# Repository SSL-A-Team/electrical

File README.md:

# Getting Started with A-Team Electrical

All current board releases use KiCad 7.X. 

See [releases](https://github.com/SSL-A-Team/electrical/releases) for competition production files. Our releases include known bug documentation, and the confirmed gerber, BoM, and CPL files sent to fab so you know you're looking and ordering what we did. Releases are accompanied by a tagged commit, for all editable project files used to generate the fab products.

For complex boards like control and kicker, we include spice models and python files that compute any relevant values from datasheets, and including documented references and links to needed formulations. 

## Setting Up KiCAD

### Setting Up the KiCAD Library Path
- Click `Preferences->Configure Paths`
- Under `Environment Variables` click `+`
- Set the name `LIB_DIR_AT`
- Set the path to `<repository_location>/lib` where \<repository_location\> is the download location.

Example entry:
- Name: `LIB_DIR_AT`
- Path: `C:\Users\guyfl\Documents\A-Team\electrical\lib`

### Setting Up JLCPCB Plugin

KiCAD version 6.99 (nightly) or newer should install the [KiCAD JLCPCB Tools](https://github.com/Bouni/kicad-jlcpcb-tools) plugin. 

## Setting Up the Python Environment
 1. We recommend creating a python environment using `python3 -m venv venv` (python 10 appears to be required)
 2. Install poetry `pip install poetry`
 3. Run any python file with `poetry run python <python_file>`
 4. (Optional) Add dependencies with `poetry add <dependency>`

## Soldering

Our [soldering process](SOLDERING.md) is documented. Advanced components like modern SMPS chips and current sense motor hardware proved sensitive to technique. The team's tries to PCBA as much as possible, but sometime it's too expensive to PCBA all chips, especially advanced ones not in stock at the fab house.

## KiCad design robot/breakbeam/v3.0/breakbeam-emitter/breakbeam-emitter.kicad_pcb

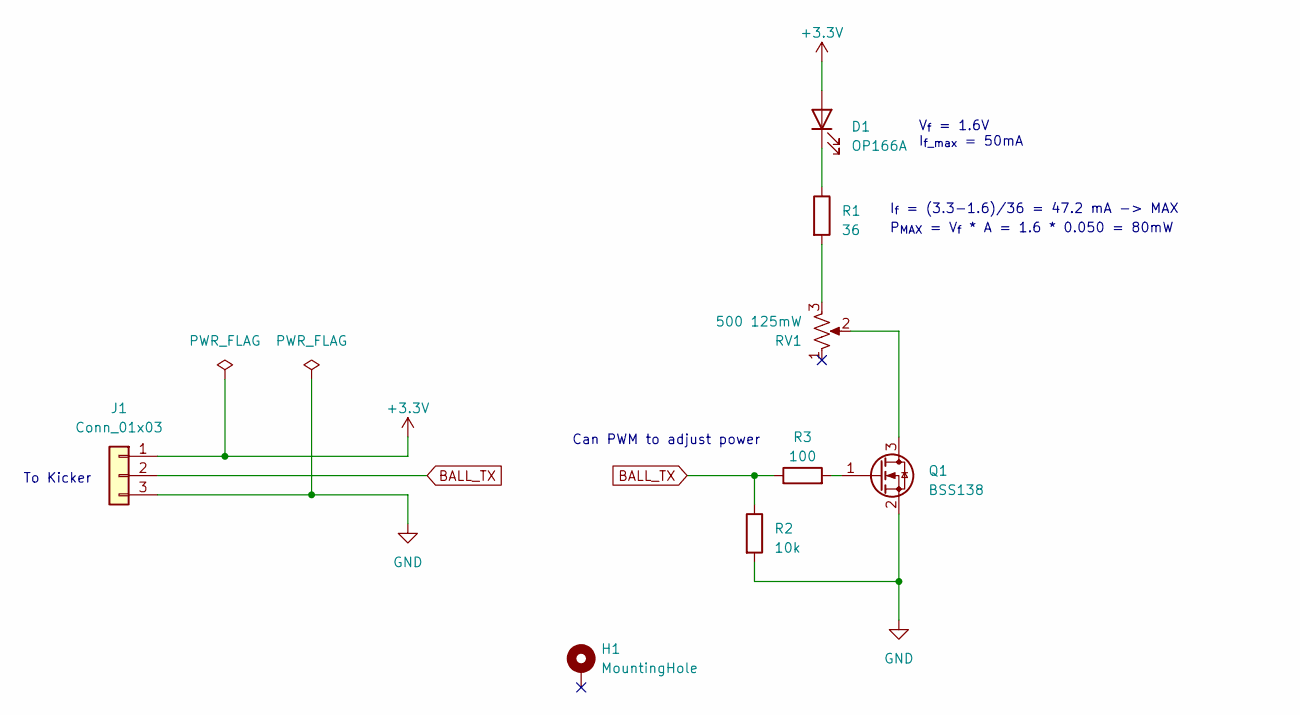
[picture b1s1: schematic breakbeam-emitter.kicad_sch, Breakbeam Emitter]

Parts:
D1: OP166A; LED_D3.0mm
H1: MountingHole; MountingHole_3.2mm_M3_ISO7380_Pad
J1: Conn_01x03; JST_SH_SM03B-SRSS-TB_1x03-1MP_P1.00mm_Horizontal; LCSC C160403
Q1: BSS138; SOT-23; LCSC C82045
R1: 36; R_0603_1608Metric_Pad0.98x0.95mm_HandSolder; LCSC C101000
R2: 10k; R_0603_1608Metric_Pad0.98x0.95mm_HandSolder; LCSC C25804
R3: 100; R_0603_1608Metric_Pad0.98x0.95mm_HandSolder; LCSC C22775
RV1: 500 125mW; Potentiometer_Bourns_TC33X_Vertical; LCSC C720649

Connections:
+3.3V: D1.2 (A), J1.1
BALL_TX: J1.2, R2.1, R3.1
GND: J1.3, Q1.2 (S), R2.2
unnamed: D1.1 (K), R1.1
unnamed: Q1.3 (D), RV1.2
unnamed: Q1.1 (G), R3.2
unnamed: R1.2, RV1.3

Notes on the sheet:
P_{MAX} = V_{f} * A = 1.6 * 0.050 = 80mW
I_{f} = (3.3-1.6)/36 = 47.2 mA -> MAX
To Kicker
V_{f} = 1.6V I_{f_max} = 50mA
Can PWM to adjust power

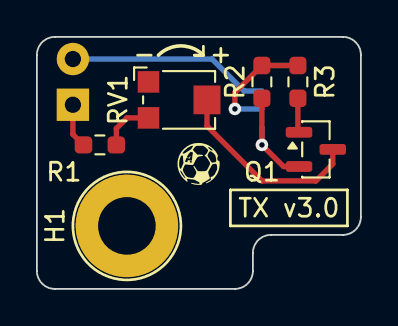
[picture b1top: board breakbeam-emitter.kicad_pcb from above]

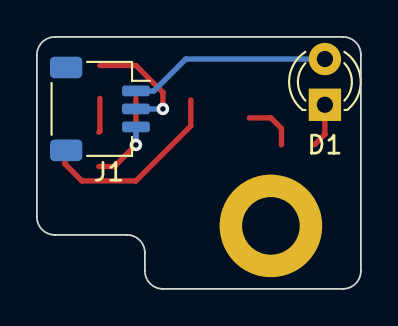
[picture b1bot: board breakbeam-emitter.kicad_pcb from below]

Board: 2 copper layers, 18.0 x 14.0 mm, 8 parts (2 on the bottom side), 7 nets.

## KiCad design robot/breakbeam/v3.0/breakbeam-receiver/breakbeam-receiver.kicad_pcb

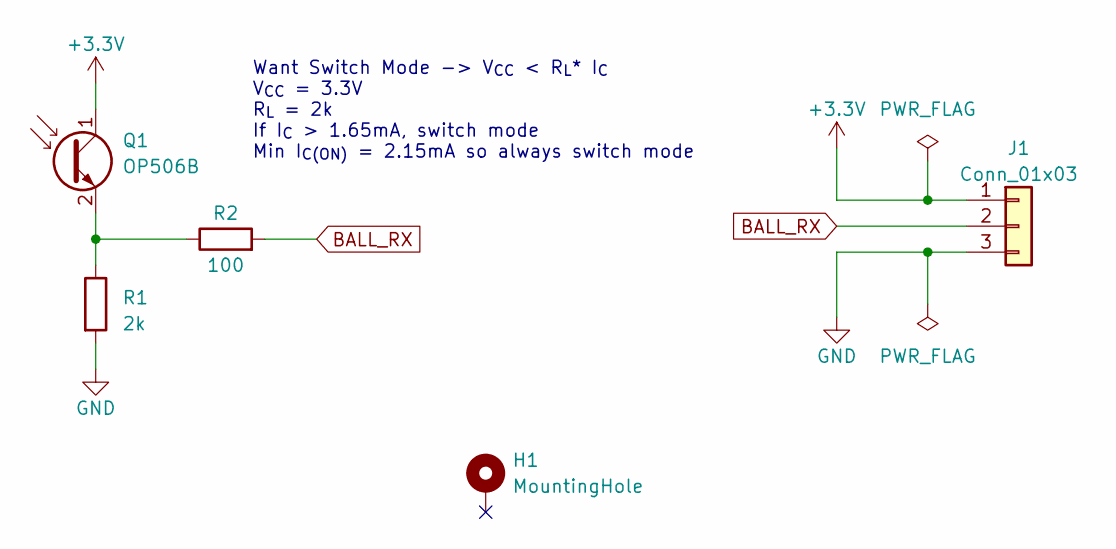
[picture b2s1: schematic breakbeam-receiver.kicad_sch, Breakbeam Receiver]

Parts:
H1: MountingHole; MountingHole_3.2mm_M3_ISO7380_Pad
J1: Conn_01x03; JST_SH_SM03B-SRSS-TB_1x03-1MP_P1.00mm_Horizontal; LCSC C160403
Q1: OP506B; LED_D3.0mm
R1: 2k; R_0603_1608Metric; LCSC C22975
R2: 100; R_0603_1608Metric; LCSC C22775

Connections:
+3.3V: J1.1, Q1.1 (C)
BALL_RX: J1.2, R2.2
GND: J1.3, R1.2
unnamed: Q1.2 (E), R1.1, R2.1

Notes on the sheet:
Want Switch Mode -> V_{CC} < R_{L}* I_{C} V_{CC} = 3.3V R_{L} = 2k If I_{C} > 1.65mA, switch mode Min I_{C(ON)} = 2.15mA so always switch mode

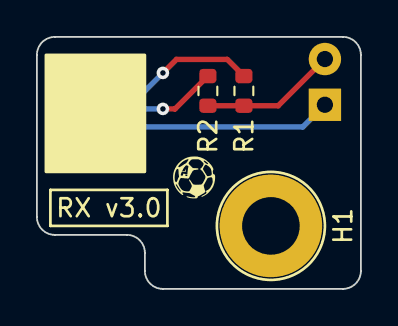
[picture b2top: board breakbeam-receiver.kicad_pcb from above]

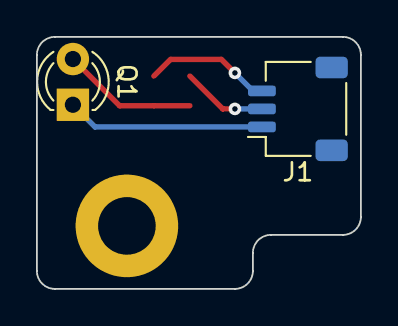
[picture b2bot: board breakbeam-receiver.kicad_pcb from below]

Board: 2 copper layers, 18.0 x 14.0 mm, 5 parts (2 on the bottom side), 4 nets.

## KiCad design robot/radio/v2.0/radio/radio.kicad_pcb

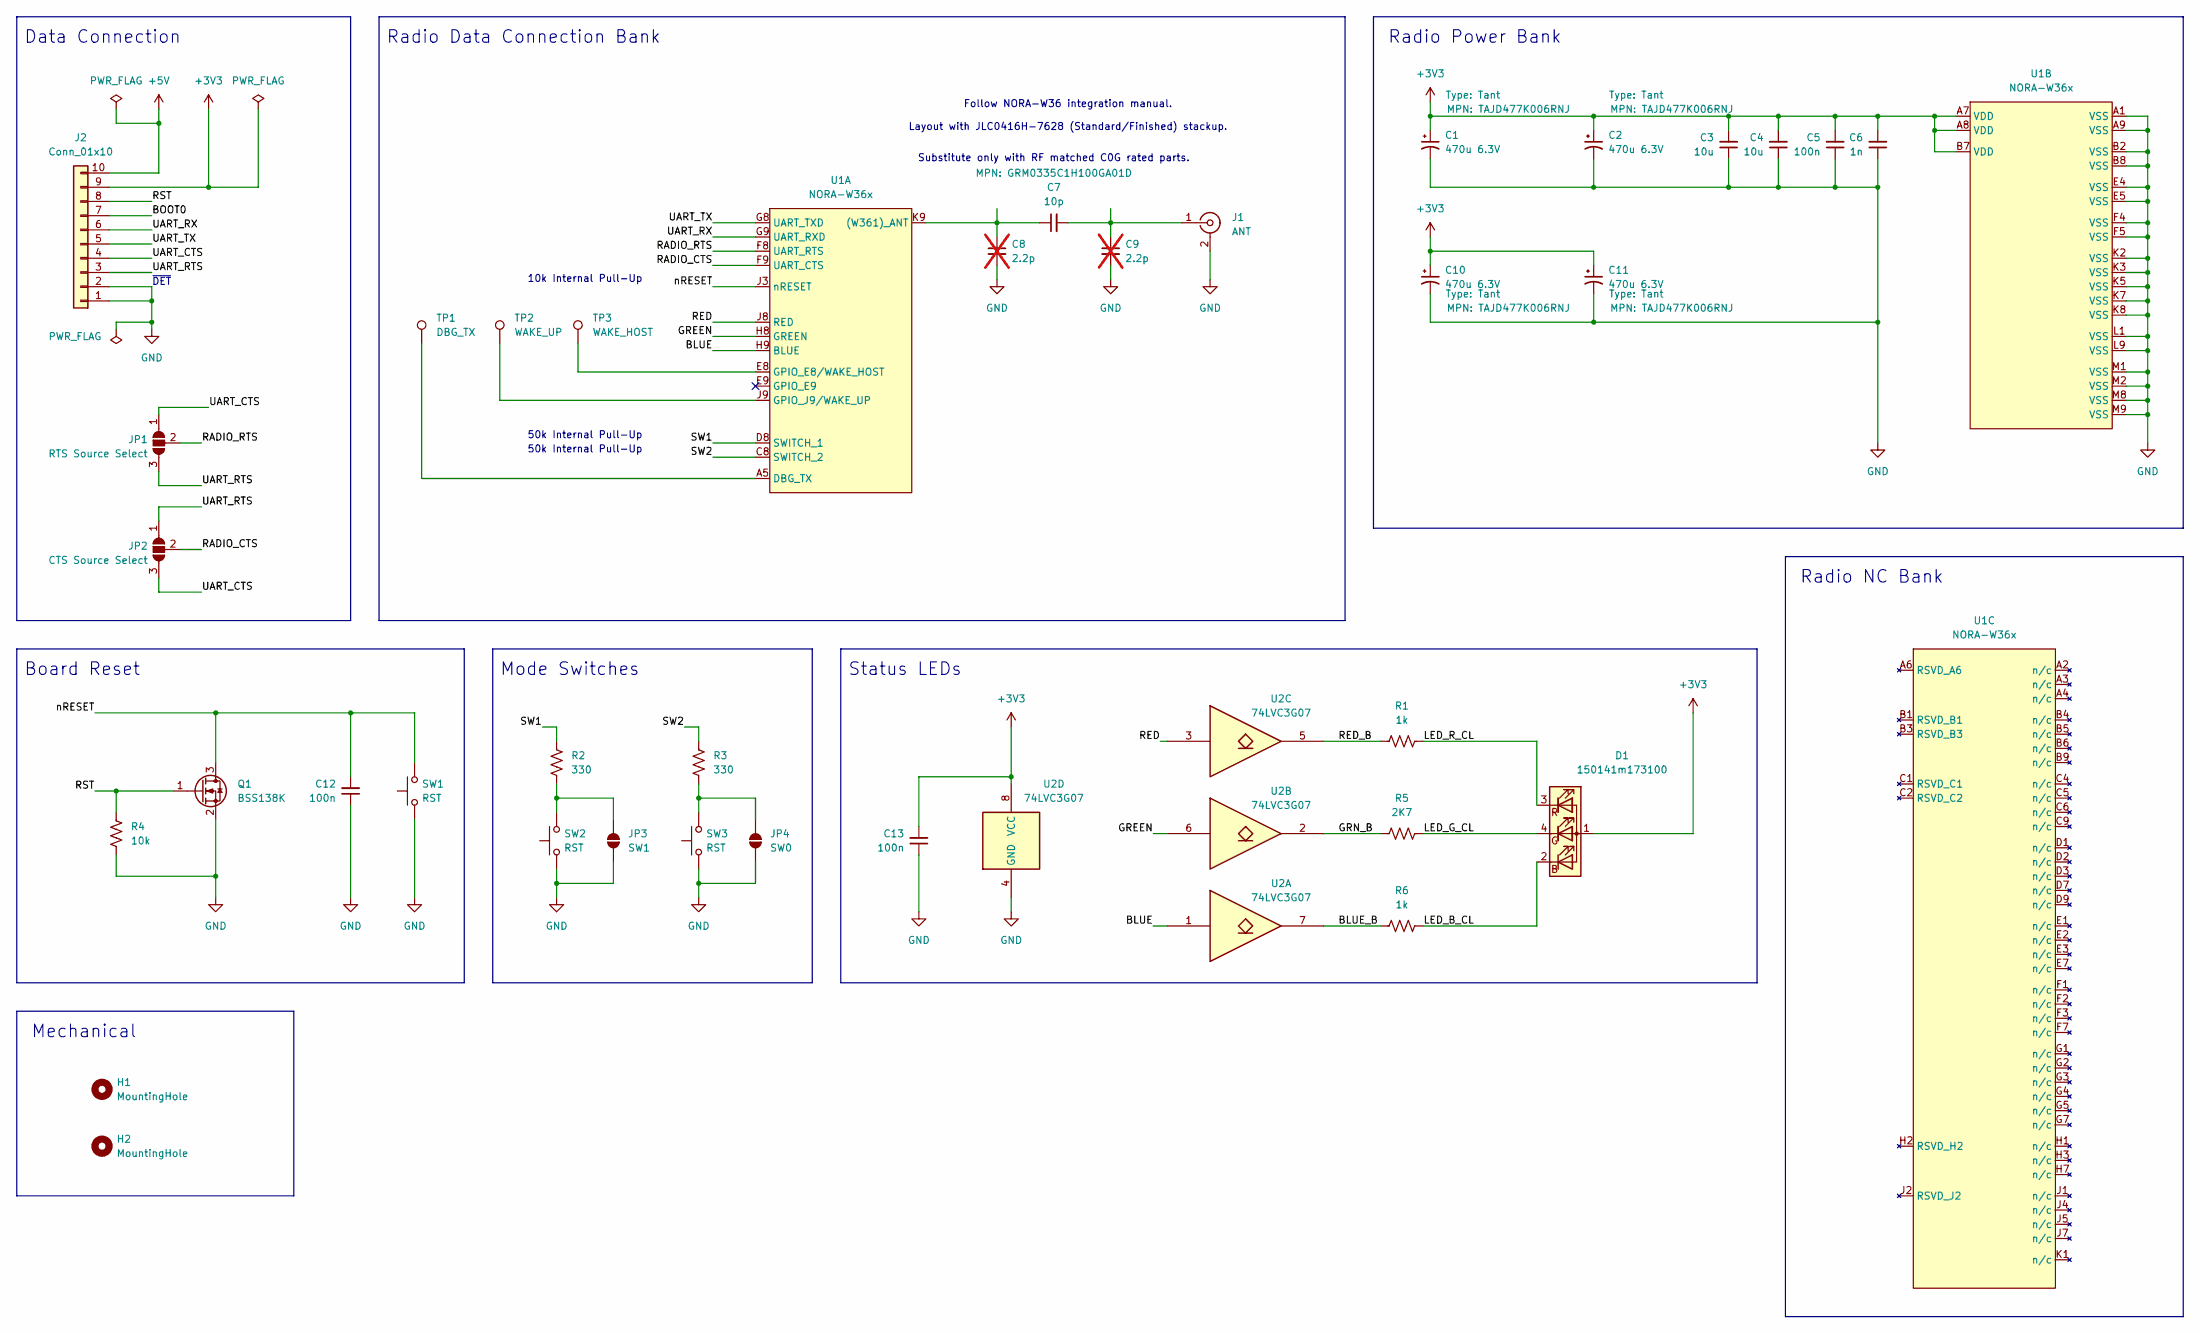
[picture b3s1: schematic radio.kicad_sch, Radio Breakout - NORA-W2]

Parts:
C1, C2, C10, C11: 470u 6.3V; CP_EIA-7343-31_Kemet-D_HandSolder; MPN TAJD477K006RNJ; LCSC C7229
C3, C4: 10u; C_0603_1608Metric; LCSC C96446
C5, C12, C13: 100n; C_0603_1608Metric; LCSC C14663
C6: 1n; C_0603_1608Metric; LCSC C100040
C7: 10p; C_0201_0603Metric; MPN GRM0335C1H100GA01D; LCSC C384956
C8, C9: 2.2p; C_0201_0603Metric; not fitted
D1: 150141m173100; LED_RGB_Wuerth-PLCC4_3.2x2.8mm_150141M173100; LCSC C5342281
H1, H2: MountingHole; MountingHole_3.2mm_M3
J1: ANT; U.FL_Hirose_U.FL-R-SMT-1_Vertical; LCSC C88374
J2: Conn_01x10; JST_SH_SM10B-SRSS-TB_1x10-1MP_P1.00mm_Horizontal; LCSC C160409
JP1: RTS Source Select; SolderJumper-3_P1.3mm_Bridged12_RoundedPad1.0x1.5mm_NumberL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
JP2: CTS Source Select; SolderJumper-3_P1.3mm_Bridged12_RoundedPad1.0x1.5mm_NumberL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
JP3: SW1; SolderJumper-2_2.0x1.2mm_Open
JP4: SW0; SolderJumper-2_2.0x1.2mm_Open
Q1: BSS138K; SOT-23; LCSC C255592
R1, R6: 1k; R_0603_1608Metric; LCSC C21190
R2, R3: 330; R_0603_1608Metric
R4: 10k; R_0603_1608Metric
R5: 2K7; R_0603_1608Metric
SW1, SW2, SW3: RST; SW_SPST_TL3305A; LCSC C2886902
TP1: DBG_TX; TestPoint_Pad_D1.5mm
TP2: WAKE_UP; TestPoint_Pad_D1.5mm
TP3: WAKE_HOST; TestPoint_Pad_D1.5mm
U1: NORA-W36x; NORA_W366
U2: 74LVC3G07; VSSOP-8_2.3x2mm_P0.5mm; LCSC C548751

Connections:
+3V3: C1.1, C2.1, C3.2, C4.2, C5.2, C6.2, C10.1, C11.1, C13.2, D1.1 (A), J2.9, U1.A7 (VDD), U1.A8 (VDD), U1.B7 (VDD), U2.8 (VCC)
+5V: J2.10
/BLUE: U1.H9 (BLUE), U2.1
/BLUE_B: R6.1, U2.7
/BOOT0: J2.7
/GREEN: U1.H8 (GREEN), U2.6
/GRN_B: R5.1, U2.2
/LED_B_CL: D1.2 (BK), R6.2
/LED_G_CL: D1.4 (GK), R5.2
/LED_R_CL: D1.3 (RK), R1.2
/RADIO_CTS: JP2.2 (C), U1.F9 (UART_CTS)
/RADIO_RTS: JP1.2 (C), U1.F8 (UART_RTS)
/RED: U1.J8 (RED), U2.3
/RED_B: R1.1, U2.5
/RST: J2.8, Q1.1 (G), R4.2
/SW1: R2.2, U1.D8 (SWITCH_1)
/SW2: R3.1, U1.C8 (SWITCH_2)
/UART_CTS: J2.4, JP1.1 (A), JP2.3 (B)
/UART_RTS: J2.3, JP1.3 (B), JP2.1 (A)
/UART_RX: J2.6, U1.G9 (UART_RXD)
/UART_TX: J2.5, U1.G8 (UART_TXD)
/nRESET: C12.2, Q1.3 (D), SW1.2, U1.J3 (nRESET)
GND: C1.2, C2.2, C3.1, C4.1, C5.1, C6.1, C8.2, C9.2, C10.2, C11.2, C12.1, C13.1, J1.2 (Ext), J2.1, J2.2, JP3.1 (A), JP4.1 (A), Q1.2 (S), R4.1, SW1.1, SW2.1, SW3.1, U1.A1 (VSS), U1.A9 (VSS), U1.B2 (VSS), U1.B8 (VSS), U1.E4 (VSS), U1.E5 (VSS), U1.F4 (VSS), U1.F5 (VSS), U1.K2 (VSS), U1.K3 (VSS), U1.K5 (VSS), U1.K7 (VSS), U1.K8 (VSS), U1.L1 (VSS), U1.L9 (VSS), U1.M1 (VSS), U1.M2 (VSS), U1.M8 (VSS), U1.M9 (VSS), U2.4 (GND)
unnamed: C7.2, C9.1, J1.1 (In)
unnamed: JP3.2 (B), R2.1, SW2.2
unnamed: JP4.2 (B), R3.2, SW3.2
unnamed: C7.1, C8.1, U1.K9 ((W361)_ANT)
unnamed: TP1.1, U1.A5 (DBG_TX)
unnamed: TP3.1, U1.E8 (GPIO_E8/WAKE_HOST)
unnamed: TP2.1, U1.J9 (GPIO_J9/WAKE_UP)

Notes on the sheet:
Radio Power Bank
50k Internal Pull-Up
Radio Data Connection Bank
Follow NORA-W36 integration manual. Layout with JLC0416H-7628 (Standard/Finished) stackup.
~{DET}
Data Connection
10k Internal Pull-Up
Board Reset
Status LEDs
Substitute only with RF matched C0G rated parts.
Mode Switches
Radio NC Bank
Mechanical

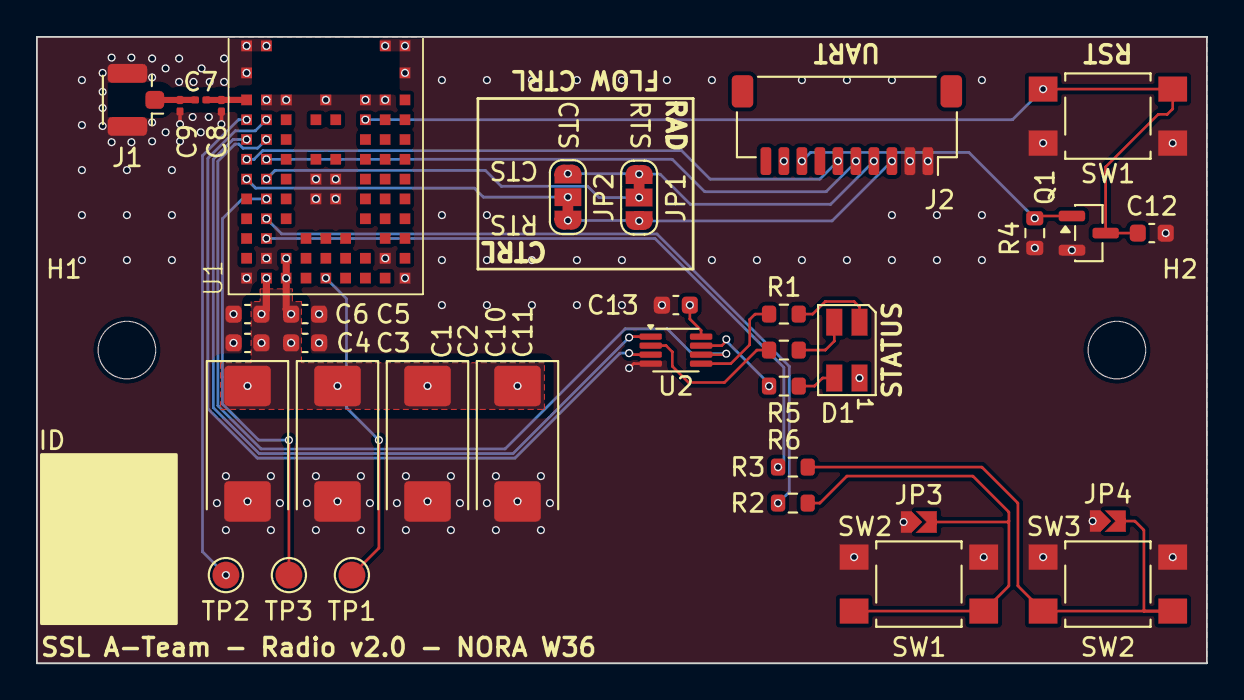
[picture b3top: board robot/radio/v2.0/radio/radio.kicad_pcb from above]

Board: 4 copper layers, 65.0 x 34.8 mm, 37 parts (0 on the bottom side), 28 nets.

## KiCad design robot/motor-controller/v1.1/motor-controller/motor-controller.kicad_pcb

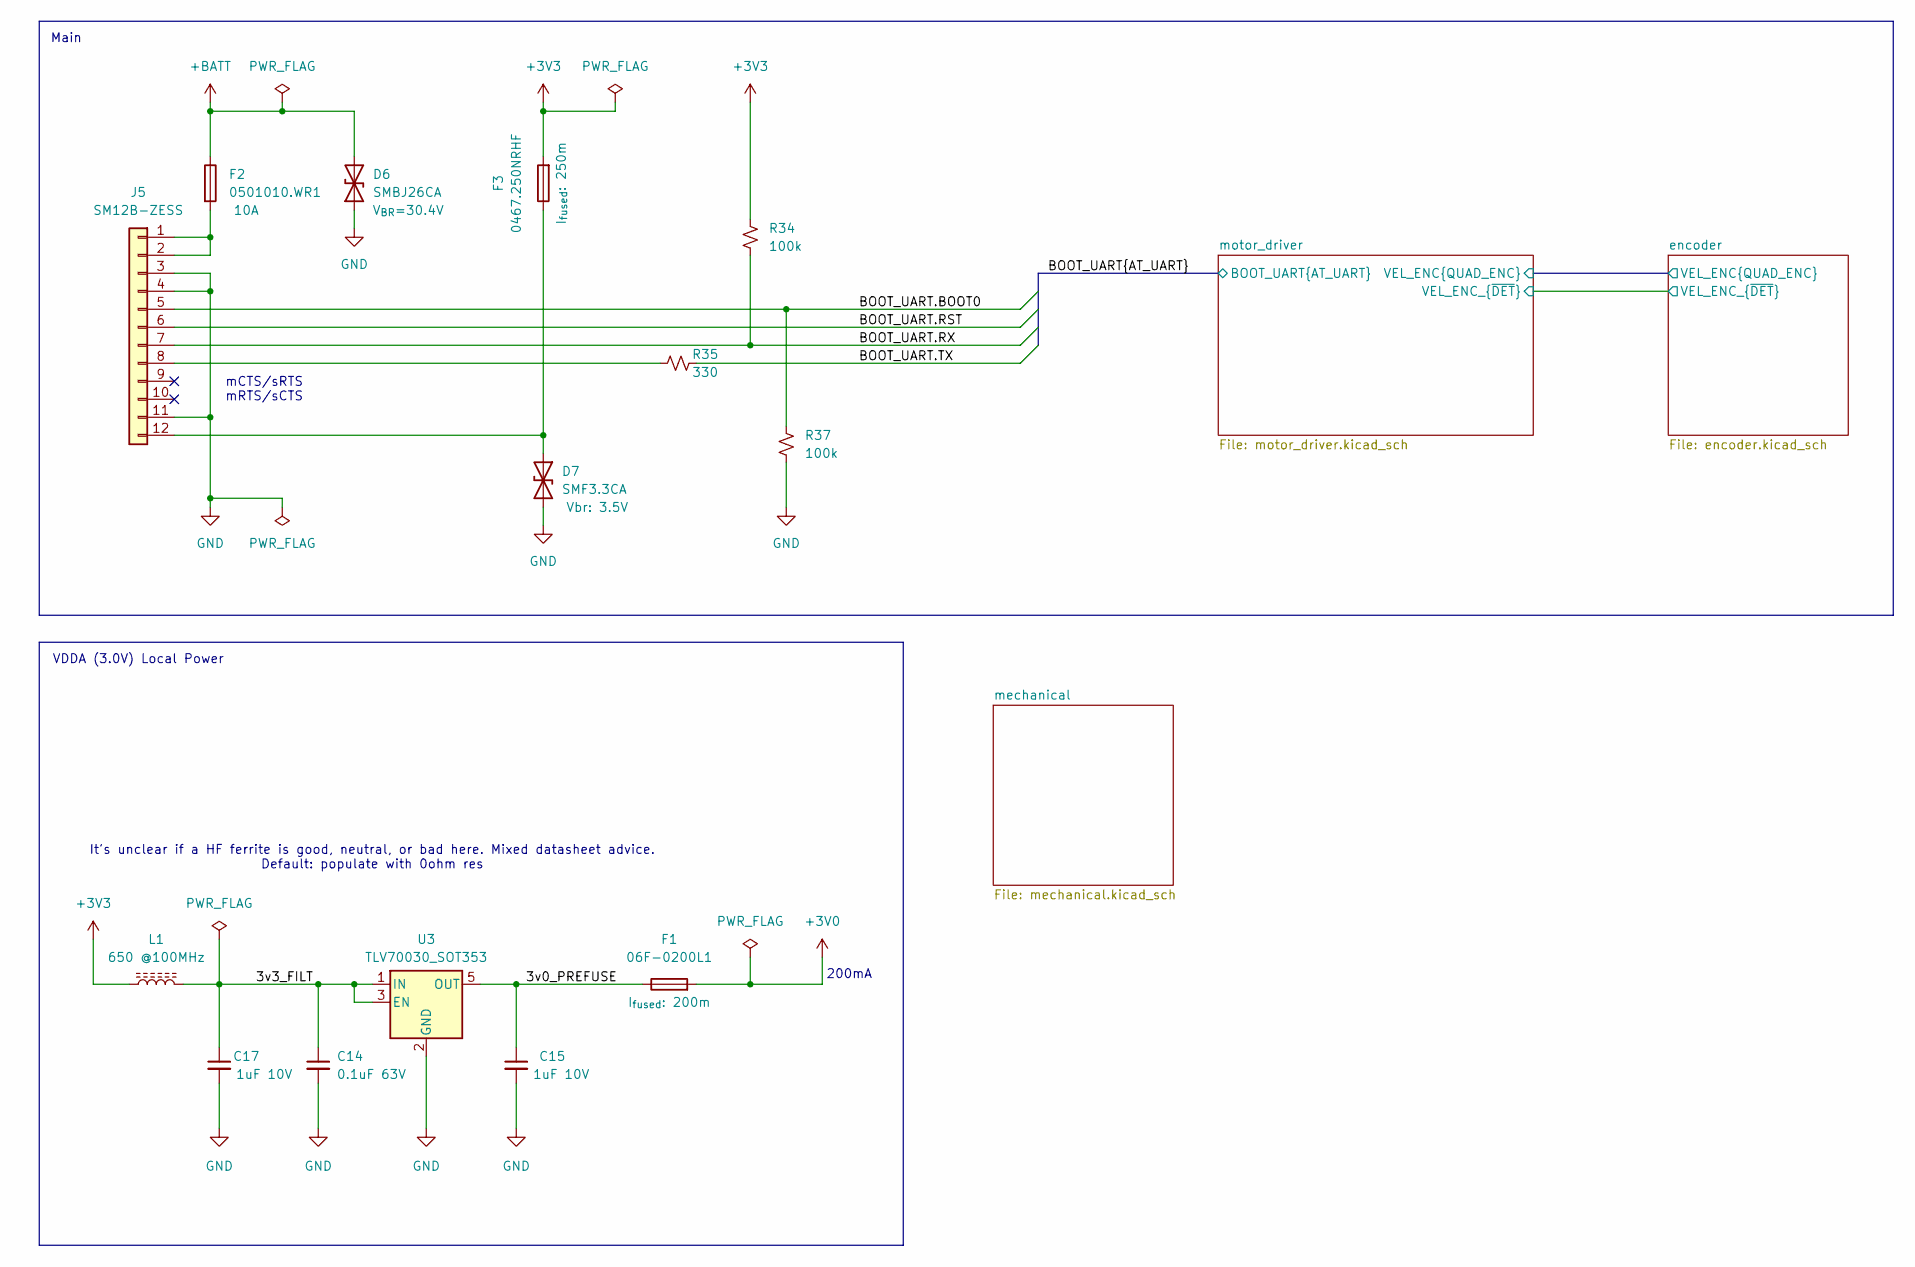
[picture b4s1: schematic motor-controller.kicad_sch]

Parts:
C14: 0.1uF 63V; C_0402_1005Metric; LCSC C131394
C15, C17: 1uF 10V; C_0402_1005Metric; LCSC C14445
D6: SMBJ26CA; D_SMB_Non-Polar; LCSC C135063
D7: SMF3.3CA; D_SOD-123; LCSC C6165153
F1: 06F-0200L1; Fuse_0603_1608Metric_Pad1.05x0.95mm_HandSolder; LCSC C377220
F2: 0501010.WR1; Fuse_1206_3216Metric_Pad1.42x1.75mm_HandSolder; LCSC C207003
F3: 0467.250NRHF; Fuse_0603_1608Metric_Pad1.05x0.95mm_HandSolder; LCSC C151137
J5: SM12B-ZESS; JST_ZE_SM12B-ZESS-TB_1x12-1MP_P1.50mm_Horizontal
L1: 650 @100MHz; R_0603_1608Metric; LCSC C21189
R34, R37: 100k; R_0402_1005Metric; LCSC C25741
R35: 330; R_0402_1005Metric; LCSC C25104
U3: TLV70030_SOT353; SOT-353_SC-70-5; LCSC C527437

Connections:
+3V0: F1.2; also elsewhere on the board
+3V3: F3.2, L1.1, R34.1; also elsewhere on the board
+BATT: D6.2 (A2), F2.1; also elsewhere on the board
/3v0_PREFUSE: C15.1, F1.1, U3.5 (OUT)
/3v3_FILT: C14.1, C17.1, L1.2, U3.1 (IN), U3.3 (EN)
/BOOT_UART.BOOT0: J5.5, R37.1; also elsewhere on the board
/BOOT_UART.RST: J5.6; also elsewhere on the board
/BOOT_UART.RX: J5.7, R34.2; also elsewhere on the board
/BOOT_UART.TX: R35.2; also elsewhere on the board
GND: C14.2, C15.2, C17.2, D6.1 (A1), D7.2 (A2), J5.3, J5.4, J5.11, R37.2, U3.2 (GND); also elsewhere on the board
unnamed: D7.1 (A1), F3.1, J5.12
unnamed: F2.2, J5.1, J5.2
unnamed: J5.8, R35.1

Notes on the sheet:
VDDA (3.0V) Local Power
It's unclear if a HF ferrite is good, neutral, or bad here. Mixed datasheet advice. Default: populate with 0ohm res
Main
200mA
mCTS/sRTS mRTS/sCTS

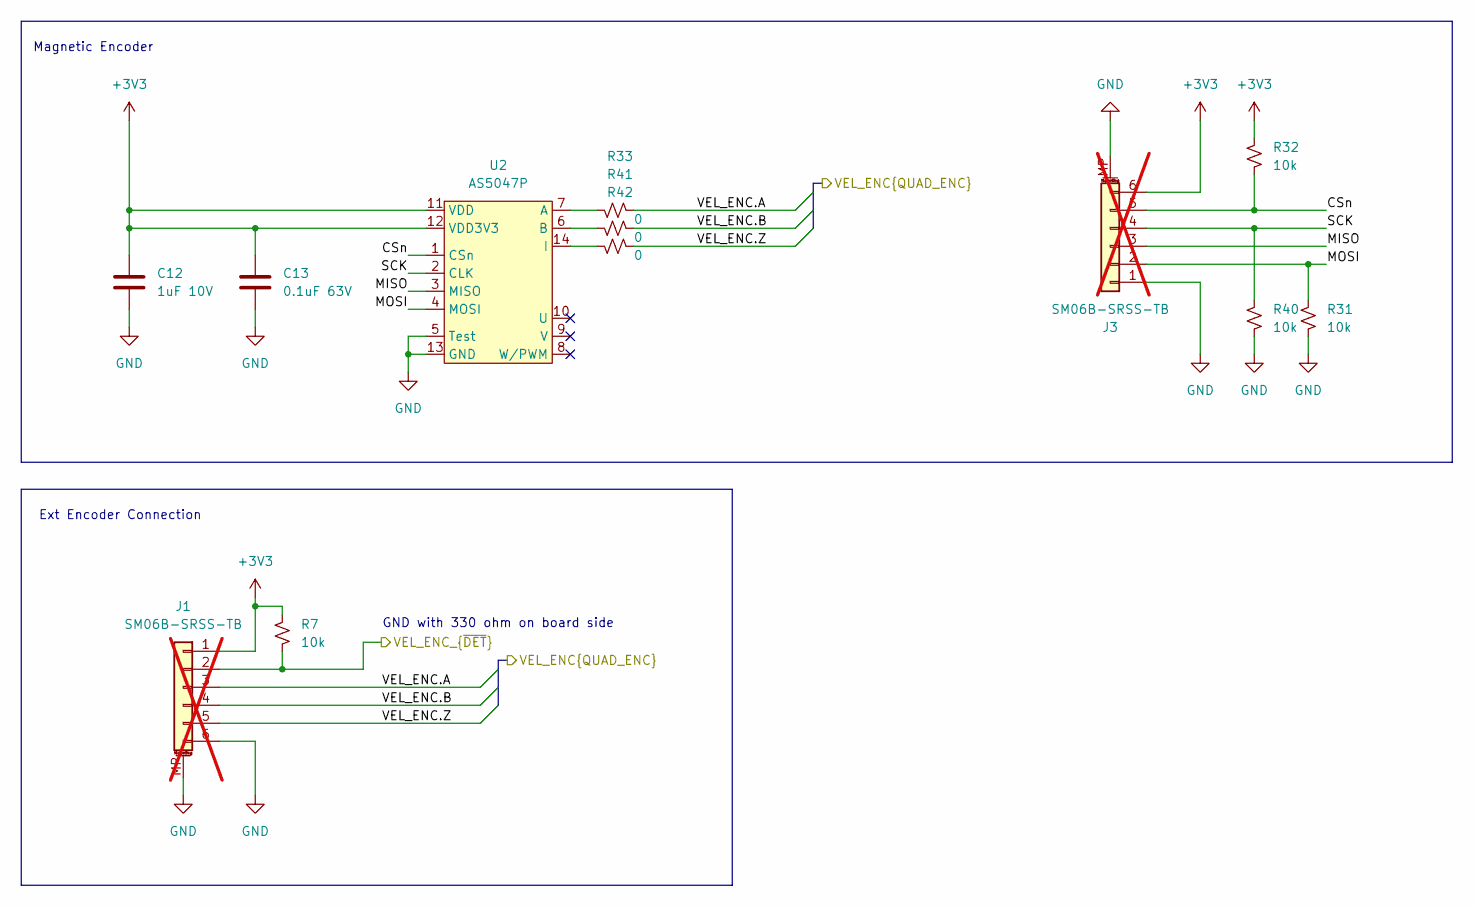
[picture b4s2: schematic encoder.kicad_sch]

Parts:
C12: 1uF 10V; C_0402_1005Metric; LCSC C14445
C13: 0.1uF 63V; C_0402_1005Metric; LCSC C131394
J1, J3: SM06B-SRSS-TB; JST_SH_SM06B-SRSS-TB_1x06-1MP_P1.00mm_Horizontal; LCSC C160405; not fitted
R7, R31, R32, R40: 10k; R_0402_1005Metric; LCSC C60490
R33, R41, R42: 0; R_0402_1005Metric; LCSC C17168
U2: AS5047P; TSSOP-14_4.4x5mm_P0.65mm; LCSC C962063

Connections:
+3V3: C12.1, C13.1, J1.1, J3.6, R7.2, R32.2, U2.11 (VDD), U2.12 (VDD3V3); also elsewhere on the board
/encoder/CSn: J3.5, R32.1, U2.1 (CSn)
/encoder/MISO: J3.3, U2.3 (MISO)
/encoder/MOSI: J3.2, R31.2, U2.4 (MOSI)
/encoder/SCK: J3.4, R40.2, U2.2 (CLK)
/encoder/VEL_ENC.A: J1.3, R33.1; also elsewhere on the board
/encoder/VEL_ENC.B: J1.4, R41.1; also elsewhere on the board
/encoder/VEL_ENC.Z: J1.5, R42.1; also elsewhere on the board
/motor_driver/VEL_ENC_{~DET}: J1.2, R7.1; also elsewhere on the board
GND: C12.2, C13.2, J1.6, J1.MP (MountPin), J3.1, J3.MP (MountPin), R31.1, R40.1, U2.5 (Test), U2.13 (GND); also elsewhere on the board
unnamed: R33.2, U2.7 (A)
unnamed: R41.2, U2.6 (B)
unnamed: R42.2, U2.14 (I)

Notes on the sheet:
Ext Encoder Connection
Magnetic Encoder
GND with 330 ohm on board side

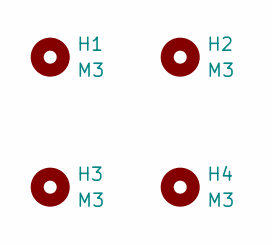
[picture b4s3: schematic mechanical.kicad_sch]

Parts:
H1, H2, H3, H4: M3; MountingHole_3.2mm_M3_Pad_TopBottom

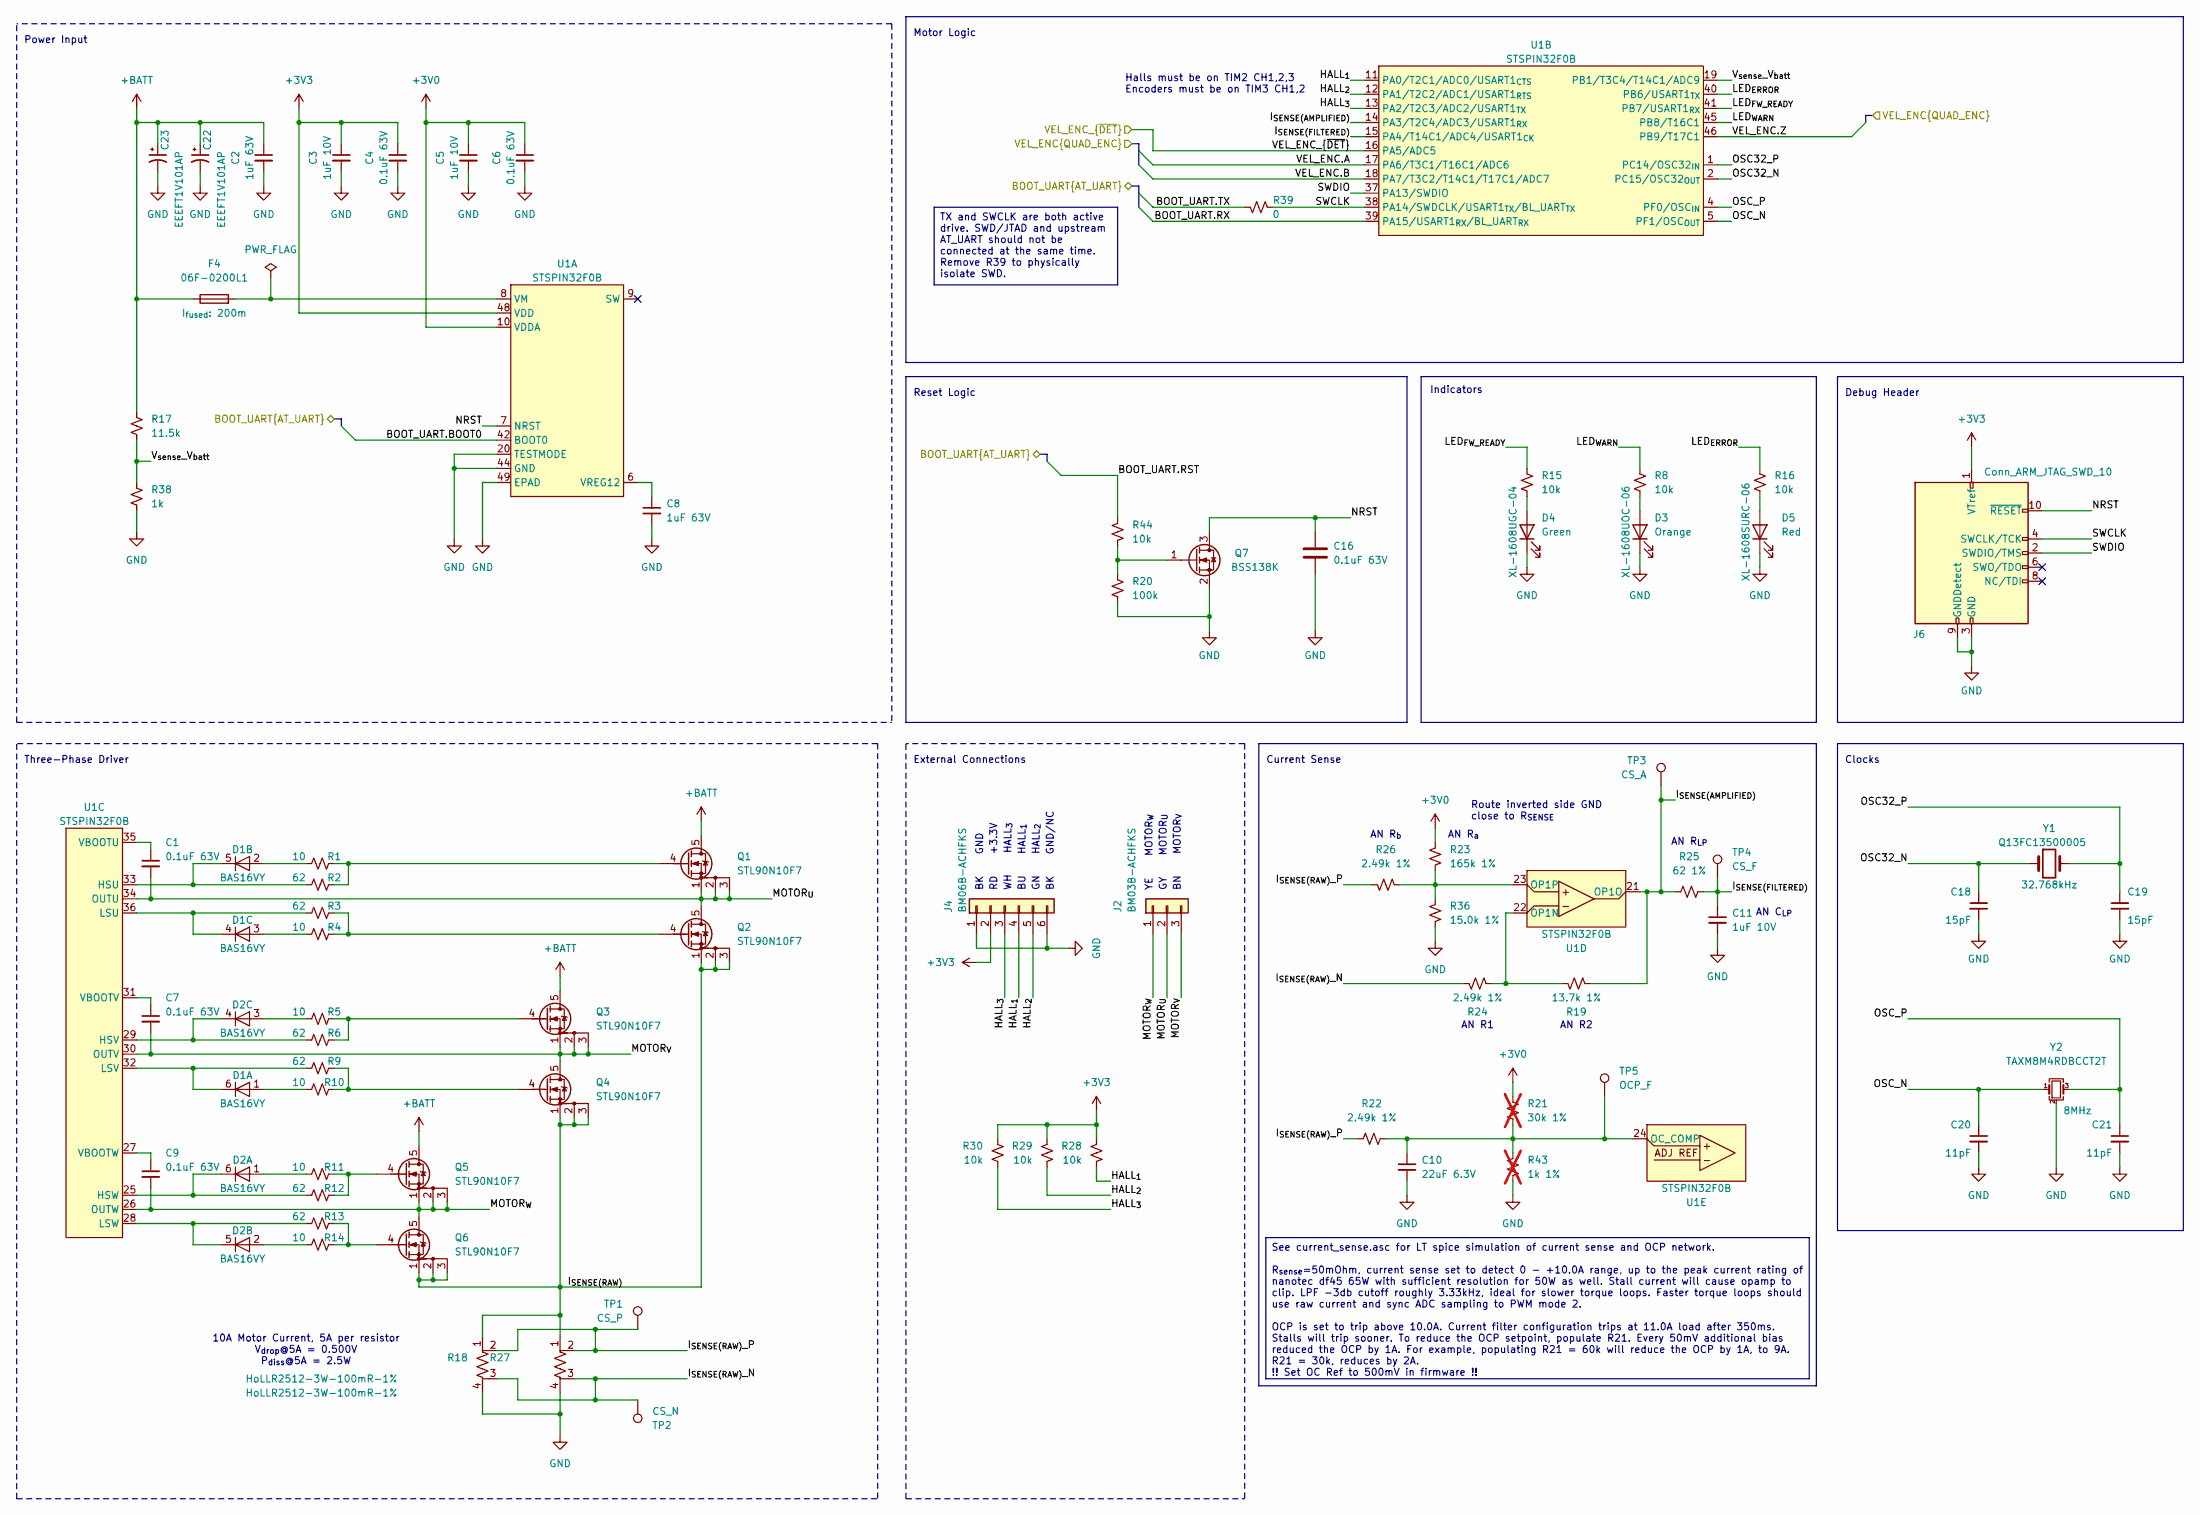
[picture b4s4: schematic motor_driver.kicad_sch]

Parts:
C1, C4, C6, C7, C9, C16: 0.1uF 63V; C_0402_1005Metric; LCSC C131394
C2, C8: 1uF 63V; C_1206_3216Metric; LCSC C70463
C3, C5, C11: 1uF 10V; C_0402_1005Metric; LCSC C14445
C10: 22uF 6.3V; C_0402_1005Metric; LCSC C415703
C18, C19: 15pF; C_0402_1005Metric; LCSC C86285
C20, C21: 11pF; C_0402_1005Metric; LCSC C161525
C22, C23: EEEFT1V101AP; CP_Elec_6.3x5.8; LCSC C128464
D1, D2: BAS16VY; SOT-363_SC-70-6; LCSC C135826
D3: XL-1608UOC-06; LED0603; LCSC C965800
D4: XL-1608UGC-04; LED0603; LCSC C965804
D5: XL-1608SURC-06; LED0603; LCSC C965799
F4: 06F-0200L1; Fuse_0603_1608Metric_Pad1.05x0.95mm_HandSolder; LCSC C377220
J2: BM03B-ACHFKS; JST_ACHFR_03V; LCSC C5177195
J4: BM06B-ACHFKS; JST_ACHFR_06V; LCSC C5304907
J6: Conn_ARM_JTAG_SWD_10; Samtec-2x5pin-1.27mm; LCSC C448647
Q1, Q2, Q3, Q4, Q5, Q6: STL90N10F7; PowerFLAT_5x6; LCSC C457493
Q7: BSS138K; SOT-23; LCSC C5224263
R1, R4, R5, R10, R11, R14: 10; R_0402_1005Metric; LCSC C25077
R2, R3, R6, R9, R12, R13: 62; R_0402_1005Metric; LCSC C100501
R8, R15, R16, R28, R29, R30, R44: 10k; R_0402_1005Metric; LCSC C60490
R17: 11.5k; R_0402_1005Metric; LCSC C270653
R18, R27: HoLLR2512-3W-100mR-1%; 2512_CS_ADI-TypeC; LCSC C2994646
R19: 13.7k 1%; R_0402_1005Metric; LCSC C852522
R20: 100k; R_0402_1005Metric; LCSC C25741
R21: 30k 1%; R_0402_1005Metric; LCSC C25776; not fitted
R22, R24, R26: 2.49k 1%; R_0402_1005Metric; LCSC C852700
R23: 165k 1%; R_0402_1005Metric; LCSC C1509613
R25: 62 1%; R_0402_1005Metric; LCSC C852875
R36: 15.0k 1%; R_0402_1005Metric; LCSC C853539
R38: 1k; R_0402_1005Metric; LCSC C11702
R39: 0; R_0402_1005Metric; LCSC C17168
R43: 1k 1%; R_0402_1005Metric; LCSC C11702; not fitted
TP1: CS_P; TestPoint_Pad_D1.5mm
TP2: CS_N; TestPoint_Pad_D1.5mm
TP3: CS_A; TestPoint_Pad_D1.5mm
TP4: CS_F; TestPoint_Pad_D1.5mm
TP5: OCP_F; TestPoint_Pad_D1.5mm
U1: STSPIN32F0B; QFN-48-1EP_7x7mm_P0.5mm_EP2.8x2.8mm; LCSC C1521053
Y1: Q13FC13500005; Crystal_SMD_3215-2Pin_3.2x1.5mm; LCSC C841881
Y2: TAXM8M4RDBCCT2T; Crystal_SMD_3225-4Pin_3.2x2.5mm; LCSC C400090

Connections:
+3V0: C5.1, C6.1, R21.1, R23.1, U1.10 (VDDA); also elsewhere on the board
+3V3: C3.1, C4.1, J4.2, J6.1 (VTref), R28.1, R29.1, R30.1, U1.48 (VDD); also elsewhere on the board
+BATT: C2.1, C22.1, C23.1, F4.1, Q1.5 (D), Q3.5 (D), Q5.5 (D), R17.1; also elsewhere on the board
/BOOT_UART.BOOT0: U1.42 (BOOT0); also elsewhere on the board
/BOOT_UART.RST: R44.1; also elsewhere on the board
/BOOT_UART.RX: U1.39 (PA15/USART1_{RX}/BL_UART_{RX}); also elsewhere on the board
/BOOT_UART.TX: R39.1; also elsewhere on the board
/encoder/VEL_ENC.A: U1.17 (PA6/T3C1/T16C1/ADC6); also elsewhere on the board
/encoder/VEL_ENC.B: U1.18 (PA7/T3C2/T14C1/T17C1/ADC7); also elsewhere on the board
/encoder/VEL_ENC.Z: U1.46 (PB9/T17C1); also elsewhere on the board
/motor_driver/HALL_{1}: J4.4, R28.2, U1.11 (PA0/T2C1/ADC0/USART1_{CTS})
/motor_driver/HALL_{2}: J4.5, R29.2, U1.12 (PA1/T2C2/ADC1/USART1_{RTS})
/motor_driver/HALL_{3}: J4.3, R30.2, U1.13 (PA2/T2C3/ADC2/USART1_{TX})
/motor_driver/I_{SENSE(AMPLIFIED)}: R19.2, R25.1, TP3.1, U1.14 (PA3/T2C4/ADC3/USART1_{RX}), U1.21 (OP1O)
/motor_driver/I_{SENSE(FILTERED)}: C11.1, R25.2, TP4.1, U1.15 (PA4/T14C1/ADC4/USART1_{CK})
/motor_driver/I_{SENSE(RAW)}: Q2.1 (S), Q2.2 (S), Q2.3 (S), Q4.1 (S), Q4.2 (S), Q4.3 (S), Q6.1 (S), Q6.2 (S), Q6.3 (S), R18.1, R27.1
/motor_driver/I_{SENSE(RAW)}_N: R18.3, R24.1, R27.3, TP2.1
/motor_driver/I_{SENSE(RAW)}_P: R18.2, R22.1, R26.1, R27.2, TP1.1
/motor_driver/LED_{ERROR}: R16.1, U1.40 (PB6/USART1_{TX})
/motor_driver/LED_{FW_READY}: R15.1, U1.41 (PB7/USART1_{RX})
/motor_driver/LED_{WARN}: R8.1, U1.45 (PB8/T16C1)
/motor_driver/MOTOR_{U}: C1.2, J2.2, Q1.1 (S), Q1.2 (S), Q1.3 (S), Q2.5 (D), U1.34 (OUTU)
/motor_driver/MOTOR_{V}: C7.2, J2.3, Q3.1 (S), Q3.2 (S), Q3.3 (S), Q4.5 (D), U1.30 (OUTV)
/motor_driver/MOTOR_{W}: C9.2, J2.1, Q5.1 (S), Q5.2 (S), Q5.3 (S), Q6.5 (D), U1.26 (OUTW)
/motor_driver/NRST: C16.1, J6.10 (~RESET), Q7.3 (D), U1.7 (NRST)
/motor_driver/OSC32_N: C18.1, U1.2 (PC15/OSC32_{OUT}), Y1.1
/motor_driver/OSC32_P: C19.1, U1.1 (PC14/OSC32_{IN}), Y1.2
/motor_driver/OSC_N: C20.1, U1.5 (PF1/OSC_{OUT}), Y2.1
/motor_driver/OSC_P: C21.1, U1.4 (PF0/OSC_{IN}), Y2.3
/motor_driver/SWCLK: J6.4 (SWCLK/TCK), R39.2, U1.38 (PA14/SWDCLK/USART1_{TX}/BL_UART_{TX})
/motor_driver/SWDIO: J6.2 (SWDIO/TMS), U1.37 (PA13/SWDIO)
/motor_driver/VEL_ENC_{~DET}: U1.16 (PA5/ADC5); also elsewhere on the board
/motor_driver/V_{sense}_V_{batt}: R17.2, R38.1, U1.19 (PB1/T3C4/T14C1/ADC9)
GND: C2.2, C3.2, C4.2, C5.2, C6.2, C8.2, C10.2, C11.2, C16.2, C18.2, C19.2, C20.2, C21.2, C22.2, C23.2, D3.1 (K), D4.1 (K), D5.1 (K), J4.1, J4.6, J6.3 (GND), J6.5 (GND), J6.9 (GNDDetect), Q7.2 (S), R18.4, R20.2, R27.4, R36.2, R38.2, R43.2, U1.20 (TESTMODE), U1.44 (GND), U1.49 (EPAD), Y2.2 (G), Y2.4 (G); also elsewhere on the board
unnamed: D1.1 (A), R10.1
unnamed: D1.6 (K), R9.1, U1.32 (LSV)
unnamed: D1.2 (A), R1.1
unnamed: D1.5 (K), R2.1, U1.33 (HSU)
unnamed: D1.3 (A), R4.1
unnamed: D1.4 (K), R3.1, U1.36 (LSU)
unnamed: D2.1 (A), R11.1
unnamed: D2.6 (K), R12.1, U1.25 (HSW)
unnamed: D2.2 (A), R14.1
unnamed: D2.5 (K), R13.1, U1.28 (LSW)
unnamed: D2.3 (A), R5.1
unnamed: D2.4 (K), R6.1, U1.29 (HSV)
unnamed: D3.2 (A), R8.2
unnamed: D4.2 (A), R15.2
unnamed: D5.2 (A), R16.2
unnamed: Q1.4 (G), R1.2, R2.2
unnamed: Q2.4 (G), R3.2, R4.2
unnamed: Q3.4 (G), R5.2, R6.2
unnamed: Q4.4 (G), R9.2, R10.2
unnamed: Q5.4 (G), R11.2, R12.2
unnamed: Q6.4 (G), R13.2, R14.2
unnamed: Q7.1 (G), R20.1, R44.2
unnamed: F4.2, U1.8 (VM)
unnamed: C8.1, U1.6 (VREG12)
unnamed: C1.1, U1.35 (VBOOTU)
unnamed: C7.1, U1.31 (VBOOTV)
unnamed: C9.1, U1.27 (VBOOTW)
unnamed: R19.1, R24.2, U1.22 (OP1N)
unnamed: R23.2, R26.2, R36.1, U1.23 (OP1P)
unnamed: C10.1, R21.2, R22.2, R43.1, TP5.1, U1.24 (OC_COMP)

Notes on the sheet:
Halls must be on TIM2 CH1,2,3 Encoders must be on TIM3 CH1,2
GN HALL_{2}
Route inverted side GND close to R_{SENSE}
Indicators
Three-Phase Driver
RD +3.3V
GY MOTOR_{U}
AN C_{LP}
WH HALL_{3}
AN R2
AN R_{a}
BK GND
10A Motor Current, 5A per resistor V_{drop}@5A = 0.500V P_{diss}@5A = 2.5W
AN R1
BK GND/NC
Power Input
AN R_{LP}
BN MOTOR_{V}
YE MOTOR_{W}
AN R_{b}
Current Sense
Motor Logic
External Connections
Debug Header
Clocks
Reset Logic
BU HALL_{1}
See current_sense.asc for LT spice simulation of current sense and OCP network. R_{sense}=50mOhm, current sense set to detect 0 - +10.0A range, up to the peak current rating of nanotec df45 65W with sufficient resolution for 50W as well. Stall current will cause opamp to clip. LPF -3db cutoff rough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
TX and SWCLK are both active drive. SWD/JTAD and upstream AT_UART should not be connected at the same time. Remove R39 to physically isolate SWD.
